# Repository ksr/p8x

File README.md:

# P8X — Hand-Built 8-Bit TTL CPU

A from-scratch 8-bit CPU built from ~130 74HCT logic chips on an 8-slot DIN41612 backplane. Fully microcoded; the microcode ROM images burned to the EPROMs are the same images the emulator interprets.

The machine now exists **twice**: as the TTL card set, and as an [FPGA
implementation](fpga/) of the same microarchitecture that boots the same
unmodified monitor, OS and toolchain. Both run the microcode from
`microcode/genucode.py`, and the C emulator is the golden reference for both.

The FPGA build also carries a **PGC-class graphics engine** (480x272
RGB565 panel, hardware 3D transforms, command lists, a fabric-parsed
graphics language modeled on the Matrox PG-640A) — see the
[theory of operation](docs/p8x-graphics-theory.md) and the
[graphics programmer's guide](docs/p8x-graphics-guide.md).

New to the abbreviations and signal names? See [GLOSSARY.md](GLOSSARY.md).

**Who made it:** I designed P8X, and it runs on an FPGA. Claude, Anthropic's AI, has been directly involved in its design, coding and documentation. — Ken Rother

## Architecture

- **8-bit data bus, 16-bit address bus**
- **4 × 16-bit pointer registers** (74169 up/down counters): P0 = PC, P1/P2 = general-purpose, P3 = stack pointer (empty-descending). The address bus is *always* driven by one of these — no separate MAR.
- **Registers:** A, B (ALU operands), T/T2 (hidden microcode temporaries), FLAGS (C, Z, N, V)
- **ALU:** 2 × 74181 + 74182 carry-lookahead, with a post-ALU shifter
- **Microcoded control:** 4 × 28C64 EEPROMs; ROM address = IR | step<<8 | cond<<12; **143 opcodes** defined in `microcode/genucode.py` (256 encodings available)
- **Memory map (rev E):** `$0000–$17FF` ROM (6 KB; shrunk from 8 KB 2026-09-14), `$1800–$FEFF` RAM (2× 62256; $1800–$1FFF is a scratch island), `$FF00–$FFFF` I/O (every data address is single-sourced in [`generators/gen_memmap.py`](generators/gen_memmap.py) → `memmap.inc`/`.h`/`.py`; commands pull the scratch/graphics/TPA-base symbols via `//#use mem`)

## Cards

The TTL machine is six core cards plus a PS/2 input card on the backplane, and a
bus test card for bring-up. Every board is designed and routed in **KiCad** (4-layer;
the plug-in cards are 280 × 140 mm) with orderable Gerbers in `hardware/<board>/kicad/`;
none has been fabricated yet. See [hardware/KICAD-BOARDS.md](hardware/KICAD-BOARDS.md)
and [hardware/RECONCILIATION.md](hardware/RECONCILIATION.md) (build readiness).

| Card | Function |
|------|----------|
| Control / Microcode | Clock, reset, sequencer, microcode EPROMs, IR, condition mux, front-panel |
| Register Bank | P0–P3 16-bit pointer registers, address bus drivers |
| ALU | A, B, T, T2 registers; 74181 ALU; shifter; FLAGS |
| Memory | 28C256 EEPROM (6 KB ROM window) + 2× 62256 SRAM, address decode (rev F) |
| I/O | Switches, LEDs, bus monitor, two 6850 ACIAs (RS-232, two DB9s) |
| CF-IDE | Two CompactFlash drives in 8-bit True IDE mode, at $FF10–$FF17 and $FF18–$FF1F |
| PS/2 | Keyboard + mouse ports at $FF58–$FF5F; an ATmega1284P behind a latch bridge |
| Bus test | Bring-up tool: a Raspberry Pi Pico drives the bus one microcycle at a time over USB |

The cards plug into a passive 8-slot backplane over a 96-pin DIN 41612 bus (rev C2).
The Eagle CAD of the first board generation is frozen (rev E) in each board's
`eagle-deprecated/` directory.

## Toolchain

| Tool | Location | Purpose |
|------|----------|---------|
| `microcode/genucode.py` | `microcode/` | Microcode generator → `u0–u3.bin` EPROM images |
| `assembler/p8xasm.py` | `assembler/` | Two-pass assembler, shares opcode table with genucode.py |
| `emulator/p8xemu.c` | `emulator/` | Cycle-accurate emulator, interprets the same u0–u3.bin images |
| `firmware/p8xmon.asm` | `firmware/` | ROM monitor (E/D/I/F/B/G/? commands) + BIOS jump table at `$0100` |
| `os/p8xos.asm` | `os/` | P8X/OS, RAM-resident disk OS booted from CF ([guide](os/README.md)) |
| `tools/p8xfs.py` | `tools/` | Host-side P8XFS disk-image tool (create/boot/put/get/ls) |
| `basic/p8xbasic.asm` | `basic/` | BASIC interpreter — disk-bootable or run-from-OS builds ([guide](basic/README.md)) |
| `apps/p8xedit.asm`, `apps/p8xasm.asm`, `apps/p8xcc.asm` | `apps/` | On-target toolchain: line editor + native two-pass assembler + native C compiler (`cc`), as `/bin` programs ([guide](apps/README.md)) |
| `compiler/p8cc.py` | `compiler/` | C cross-compiler (subset) → P8X asm → RUNnable `.bin` ([guide](compiler/README.md)) |
| `generators/gen_p8xopc.py` | `generators/` | Opcode table for the native assembler, generated from `genucode.OPC` |
| `generators/gen_eagle.py` | `generators/` | The canonical board netlists (`CARDS`, `busnet()`); its Eagle output is frozen at rev E |
| `generators/gen_kicad.py`, `build.sh` | `generators/` | KiCad boards from those netlists: placement, Freerouting, Gerbers, and the ERC/DRC readiness check |

**Generators are canon.** Never hand-edit board files (`.kicad_pcb`, and the frozen Eagle `.sch`/`.brd`) or ROM binaries — they are build artifacts. Edit the generator and regenerate. See [generators/README.md](generators/README.md) for what each script does and how to run it.

## Quick Start

Setting up a new machine? See [SETUP.md](SETUP.md) for the full toolchain, tier by
tier, and run `python3 tools/setup_check.py` to see what is installed and what each
work area still needs. Only the core-software tier is required to build and test.

```sh
# Build the emulator and regenerate microcode images
cd emulator && make

# Run the smoke tests (message print, JSR/RTS round-trip, branch countdown)
make test

# Rebuild a KiCad board: placement -> Freerouting -> Gerbers + renders -> the
# ERC/gate-sim/DRC/keepout/fab readiness check (needs KiCad 10 and a Freerouting
# jar; `all` builds every board). The netlists come from generators/gen_eagle.py.
cd ..
sh generators/build.sh memory-card
sh generators/check_card.sh memory-card          # the readiness check alone

# Reference PDFs (run from anywhere):
cd hardware
python3 ../generators/gen_bus_pdf.py              # bus definition PDF (hardware/backplane/)
python3 ../microcode/gen_progguide.py             # programmer's guide (-> docs/)
```

### EEPROM / programmer images

Both build paths emit **Intel HEX** alongside the raw `.bin`, for loading into an
EEPROM programmer:

- **Microcode** — `microcode/genucode.py` writes `u0–u3.bin` (what the emulator
  and tests load); the matching Intel HEX for the four 28C64 control-store EPROMs
  is produced into `rom/` by `make rom` (see below).
- **Program ROM** — the assembled monitor + BIOS for the 28C256 at `$0000`
  (about 4.9 KB of the 6 KB window; BASIC is no longer ROM-resident). `make rom` builds it into `rom/`.
- **Any other binary** — `python3 tools/bin2hex.py in.bin out.hex [base]`
  (e.g. a monitor built directly with `p8xasm.py`).

For a ready-to-burn set at fixed paths, run `cd emulator && make rom` (or
`sh tools/build_rom.sh`). It refreshes the four control-store EPROMs in
`microcode/` and writes the program ROM to `rom/p8x-prog-rom.{bin,hex}`. Both
are committed; see [rom/README.md](rom/README.md) for the chip map.

## Documentation

The documents below are also built into the project website, [p8x.cottageworker.com](https://p8x.cottageworker.com) (`website/`, MkDocs; published on every push to `main`).

| Document | Description |
|----------|-------------|
| [hardware/backplane/p8x-bus-definition.md](hardware/backplane/p8x-bus-definition.md) | Authoritative 96-pin bus pinout, signal descriptions, DOE/DLD encoding, microcode word layout |
| [hardware/backplane/p8x-backplane-design.md](hardware/backplane/p8x-backplane-design.md) | PCB stackup, termination analysis, BOM |
| [docs/p8x-card-standards.md](docs/p8x-card-standards.md) | Design rules that apply to every plug-in card |
| [docs/p8x-system-design.md](docs/p8x-system-design.md) | System and card-by-card architecture reference |
| [hardware/cf-card/p8x-cf-os-design.md](hardware/cf-card/p8x-cf-os-design.md) | CF-IDE hardware + P8X/OS design |
| [hardware/cf-card/p8xfs-v2-hierarchical.md](hardware/cf-card/p8xfs-v2-hierarchical.md) | P8XFS v2 hierarchical filesystem spec |
| [docs/p8x-programmers-guide.pdf](docs/p8x-programmers-guide.pdf) | Generated instruction set reference |
| [basic/p8x-basic-guide.md](basic/p8x-basic-guide.md) | P8X BASIC language reference (statements, expressions, graphics, examples) |
| [fpga/README.md](fpga/README.md) | FPGA build: milestones, getting started, both paths |
| [fpga/docs/architecture.md](fpga/docs/architecture.md) | FPGA module hierarchy, peripheral map, graphics, co-sim spec |
| [fpga/rtl/README.md](fpga/rtl/README.md) | What is shared vs sim-only, and the `cen` / `sc_en` contracts |
| [fpga/sim/README.md](fpga/sim/README.md) | How the co-sim trace-diff works, and the graphics frame diff |
| [BACKLOG.md](BACKLOG.md) | Live work only: NEXT / IDEAS / VERIFY / WONT-DO |
| [BACKLOG-DONE.md](BACKLOG-DONE.md) | Completed work + the project log |

### Per-card guides

Each board has its own directory under `hardware/` holding everything about it —
the KiCad board and its Gerbers, placement PDF and renders (`kicad/`), a README
explaining how the circuit works chip by chip, any board-specific design docs, and
the frozen Eagle files (`eagle-deprecated/`):

| Card | Directory |
|------|-----------|
| Control / Microcode | [hardware/control-card/](hardware/control-card/README.md) |
| Register Bank | [hardware/regbank-card/](hardware/regbank-card/README.md) |
| ALU | [hardware/alu-card/](hardware/alu-card/README.md) |
| Memory | [hardware/memory-card/](hardware/memory-card/README.md) |
| I/O | [hardware/io-card/](hardware/io-card/README.md) |
| CF-IDE | [hardware/cf-card/](hardware/cf-card/README.md) |
| PS/2 | [hardware/ps2-card/](hardware/ps2-card/README.md) |
| Bus test | [hardware/bustest-card/](hardware/bustest-card/p8x-bustest-card-design.md) |
| Backplane | [hardware/backplane/](hardware/backplane/p8x-backplane-design.md) |

## FPGA implementation

A standalone [FPGA build](fpga/) on a **Sipeed Tang Nano 20K** (Gowin GW2AR-18)
runs the whole machine — CPU, memory, ACIA console, microSD disk, and a 4.3"
480x272 graphics panel — from one chip and a USB cable. It is a **parallel track to the TTL build, not a replacement**:
same horizontal microcode word, same sequencer, same pointer/address model, so
the monitor, OS, BASIC, C compiler and assembler run **unmodified**.

| Milestone | State |
|-----------|-------|
| 0 First light (UART echo + heartbeat) | done |
| 1 CPU core in simulation, all 88 opcodes of the time | done |
| 2 ACIA + driven console in simulation | done |
| 3 Core on real hardware, full 64K map | done |
| 4 microSD disk — P8X/OS boots from card | done |
| 5 Clock-up + IRQ | next |
| 6 Graphics: 480x272 panel + drawing engine | done |

As built: **9 MHz** effective (27 MHz fabric, three phases per microcycle). The
CPU-only build is 40/46 block RAMs at ~48 MHz Fmax; adding the graphics panel takes
it to 44/46 and 13288/20736 LUT4, with Fmax measured at 38.8 MHz — still four times
the clock it runs at. P8X is programmed into the board's flash, so it comes up
standalone on power.

**Graphics** (`build.sh lcd`) adds the panel's native 480×272 framebuffer in
**RGB565 direct colour** — a pixel IS its colour, 65,536 of them — living in
the Tang Nano's in-package SDRAM behind a streaming controller, with a drawing
engine driven by BASIC in one window-space coordinate system (y up, the
PGC's own): `COLOR r,g,b` (or one packed value), `CLS`, `PIXELW`, `LINE`,
`BOX`, `CIRCLE` (a second radius gives an ellipse), `IMAGE` (draws a
P8I picture file — `tools/p8img.py` converts anything into one), the
`PIXELR(x,y)` and `RGB(r,g,b)` functions — plus the full PGC graphics
language as native statements (`MOVE`/`DRAW`/`POLY`/`RECT`, matrices, 3D,
command lists; see `man basic`). Text is the PGC's own stroke `TEXT`,
drawn card-side from the font the OS streams from `/FONT.GL` at boot
(GTEXT and its software rasterizer retired 2026-09-01). The drawing
statements emit that language; the engine lives in the device, so a
filled box costs the same handful of instructions as an empty one.
There is one geometry and no modes or palette to manage.
The same device is modelled in `p8xemu`, and the two are byte-compared frame
by frame.

**3D** (stages 7–8, `fpga/tang-nano-20k/sdram/STAGE*.md`): a wireframe
pipeline available three ways from C — all in software (`//#use gfx` +
`//#use g3d`), accelerated by the **MDU** (a memory-mapped hardware
multiply-divide unit at `$FF30`), or fully in fabric via the **geometry
engine** (`$FF40`): edge lists in SDRAM, an S7.8 matrix, one command to
transform/clip/project/draw, and page-flipped double buffering. The same
program picks the fastest fitted path at runtime; `cube` on the shipped disk
demonstrates all of them (`man cube`, `man g3d`).

**Verification is the point.** Every milestone is "make the RTL match the
emulator": the same program runs on both and their per-cycle architectural state
is diffed, so a divergence is a bug with an exact microcycle and signal rather
than a mystery. `fpga/sim/isa_test.asm` drives the original 88 opcodes through that diff;
the 55 added since are microcode only (no new hardware), and the RTL runs them from
the same images.

```sh
fpga/sim/run.sh 60000 isa_test.asm          # co-sim, the original 88 opcodes
fpga/sim/console.sh "" os/run-disk.img      # interactive console on the RTL
fpga/tang-nano-20k/build.sh cpu load        # build + program the board
```

## Status

- Emulator working: 143 opcodes, ACIA on stdin/stdout, CF-IDE disk model (`-c `), interactive I/O card (switches `-s`, LED trace `-L`), verified against microcode images
- Assembler working: two-pass, full expression support, shares opcode table with microcode generator
- KiCad boards designed and routed for the six CPU cards, the PS/2 card, the bus test card and the backplane (9 boards, 0 unconnected, Gerbers in each `kicad/`); none fabricated yet. The Eagle files of the first generation are frozen in `eagle-deprecated/`. (The standalone LED test card was a CAD-workflow trial, never built — deprecated and moved to `hardware/deprecated/led-card/`; its I/O address `$FF0C` is now free.)
- ROM monitor boots in the emulator; its filesystem hooks (`I`/`F`/`B`) run end to end against a CF image (`make test-cf`)
- P8X/OS v1.0 — full shell over flat **and hierarchical (P8XFS v2)** volumes. Built-in commands: `cd`/`mkdir`/`rmdir`/`load`/`run`/`save`/`del`/`path`/`pack`/`fsck`/`format`/`mount`/`umount`/`help`/`exit`/`man`/`sh`/`make`/`bootload` (`make` builds a target from a CWD `Makefile`; `bootload file` installs a freshly-built OS image into the boot sectors so the next `exit`+`B` runs it — the on-target OS-update step, closing the self-hosting loop) (the minimal-kernel split moved the pure-viewer/memory commands to `/bin`, including `dump`/`dep` — only `pack`/`fsck` remain resident because they mutate/scan the filesystem). **Dual CompactFlash** — a second card is **mounted at `/d1`** in one unified namespace (drive 0 is the root), so ordinary paths reach it with drive-unaware commands: `cd /d1`, `cat /d1/NOTES`, `grep x /d1/SRC/*.C`, cross-mount `cp /d1/A /B`. A single mount redirect in `FRESOLVE`/`RV_START` does the routing; **`cp -r /d1/dir /dir`** recursively copies a subtree across the mount (card provisioning), creating directories via the `SYS_MKDIR` syscall. **Userland commands in `/bin`** (written in C, run by bare name via implicit RUN + a `/bin` search PATH, or explicit `run`): **`dir`/`pwd`/`tree`/`cat`/`wc`/`grep`/`cp`/`mv`/`head`/`tail`/`more`/`sort`/`uniq`/`sed`/`awk`/`find`/`diff`/`cmp`/`vi`/`touch`/`man`/`dump`/`dep`/`examine`/`disasm`** (`dir README.TXT` lists a file / `dir R*` a glob, `dir -R`, `cp -r`, a VT100 `vi` screen editor, `man <cmd>` reading `/man`, `awk '{print $2}'` field processing, `examine` = interactive memory examine/modify like the monitor's `E`, etc.) — see [os/commands/](os/commands/README.md). Path resolution + CWD-path prompt; I/O redirection (`<`/`>`) and two-stage pipes (`a | b`); line editing (backspace/DEL, Ctrl-D EOF, **up/down-arrow command history** — an 8-line RAM ring — and **Tab autocomplete** of commands/paths with common-prefix fill + a match list on the second Tab); **`pack`** compacts the directory tree and **`fsck`** checks integrity on-target; host-side `p8xfs.py` builds (`--v2`), navigates, and `fsck`s images (`make test-os`)
- BASIC builds two ways from one source: disk-bootable (`B`) and a run-from-OS TPA program (`run BASIC.bin`) — `make test-basic` (ROM-resident BASIC was removed to reclaim ROM space; the old standalone `$0000` build was retired in 2026-08 when BASIC's console I/O moved onto the BIOS, which needs the monitor resident)
- On-target toolchain: **EDIT** (line editor) + **ASM** (native two-pass assembler) + **CC** (a from-scratch C compiler written in asm) as `/bin` programs — edit → **compile (`cc x.c >x.asm`)** → assemble → run a program entirely on the machine; ASM output is byte-identical to the host assembler across the whole opcode table (`make test-os`, see [apps/](apps/README.md)). **Rebuild any command on-target** — every command's source rides along under `/src/commands/{c,asm}` (plus shared `lib_*` helpers), each dir carrying a real **`Makefile`** (`target: deps` + TAB recipe, with `all`/`clean`/`install` targets). The **`make`** built-in reads the CWD `Makefile`, resolves prerequisites depth-first (shared deps built once), and drives `cc`→`asm` (or `asm` alone): `cd /src/commands/c && make pwd` rebuilds one command, `make all` the whole dir into `bin/`, `make install` publishes them over `/bin`, `make clean` removes the build outputs — see [os/commands/](os/commands/README.md). (P8X shell scripts end in `.sh`; `make` uses proper Makefiles.)
- **Native C compiler — Milestone B achieved.** `apps/p8xcc.asm` (`/bin/cc`) is a from-scratch, single-pass C compiler written directly in assembly, small enough to compile C **entirely on the machine** (front *and* back end) where the optimizing `p8cc.c` codegen — ~82 KB, larger than the whole 64 KB address space — never could. Through v0.28 it covers: functions, direct **and mutual** recursion, pointers + pass-by-reference, `int`/`char` arrays with `[]` and decay, **structs** (`.`/`->`), globals, the full operator set (`+ - * / % << >> & ^ | && || ?:`, `++`/`--`/`+=`/`-=`, comparisons, unary `- ! * &`), hex/char/string literals with escapes, `//`+`/* */` comments, a recursive **`//#use`** preprocessor (splices `/lib/lib_*.c`) plus object-like **`//#define`** macros (e.g. `//#use abi` names the BIOS/OS addresses so a command writes `bios(FOPEN, RDBUF, 0)`), and the `putchar`/`puts`/`getchar`/`peek`/`poke`/`argstr`/`bios` builtins. It compiles real OS command source: **`pwd.c` → `cc` → `asm` → runs** correctly on-target. Known gaps are listed under "cc — KNOWN LIMITATIONS" in `BACKLOG-DONE.md` (with the Milestone A/B record).
- **Host C compiler** — `compiler/p8cc.py` (the primary build tool: every `/bin` command is compiled with it) plus `compiler/p8cc.c`, the same compiler rewritten in its own subset that **self-compiles** ("small C in small C", Milestone A). Full subset incl. `struct`/`union`, global initializers, and the operators above (`make test-c`, host-vs-self differential `c_selfhost_test`, see [compiler/](compiler/README.md)).
- BIOS **file API**: byte streams (`FOPEN`/`FGETB`, `FWOPEN`/`FPUTB`/`FCLOSE`), path resolution into subdirectories (`FRESOLVE`), name formatting (`FNORM`), and directory iteration (`FOPENDIR`/`FNEXT`) — the assembler rides on the streams and self-hosts (`make test-cf`)
- **FPGA (Tang Nano 20K):** the same microarchitecture in Verilog, verified against the emulator cycle-for-cycle across the original 88 opcodes, then run on real hardware — monitor over USB serial, full 64K map, and **P8X/OS booting from a microSD** with the whole `/bin` toolchain. The board wrote its own disk: `fpga/tang-nano-20k/tools/imgload.asm` streams a P8XFS image over the console and writes it with `CFWRITE`, so no host root or card reader is needed. See [fpga/](fpga/README.md)
- **Next:** multi-stage pipes (`a | b | c`); open-by-name as one syscall (`SYS_OPEN`); the IRQ-controller hardware card; hardware bring-up (DIN 41612 footprint check against the physical connectors, order the backplane first); FPGA milestone 5 (clock-up + IRQ). Current state in [docs/p8x-status.md](docs/p8x-status.md), the working list in [BACKLOG.md](BACKLOG.md)

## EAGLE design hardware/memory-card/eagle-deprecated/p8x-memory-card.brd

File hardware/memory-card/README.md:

# Memory Card

> **Theory of operation:** [p8x-memory-card-theory.md](p8x-memory-card-theory.md) — deep walkthrough of inputs/outputs, signal flow, and logic.

Provides the system's ROM and RAM and gates them onto the data bus. It decodes the
address bus to pick ROM vs RAM, keeps both off the data bus during I/O accesses,
and generates a clean write strobe.

> **Build the KiCad rev F board.** The 2026-09-14 ROM shrink made the map
> **6 KB ROM `$0000–$17FF`** with **`$1800–$1FFF` a RAM scratch island** (written
> by the OS/BIOS, so it must be RAM). The KiCad board in [`kicad/`](kicad/README.md)
> (rev F, routed, not yet fabricated) implements that decode on three spare gates,
> with no new chips: ROM `!CE` gains an `A11·A12` term and low-RAM U10 widens to
> `$1800–$7FFF`. The chip-by-chip text below describes the **rev E** netlist in
> `gen_eagle.py` (8 KB ROM, `$0000–$1FFF`), which `kicad/mem_revf.py` rewires to
> rev F for both the KiCad board and its schematic; the frozen Eagle `.sch` in `eagle-deprecated/` is rev E too and
> must not be built.

| Region | Device | Size |
|--------|--------|------|
| `$0000–$17FF` | 28C64 ROM (U1) | 6 KB — monitor + BIOS (BASIC is a disk program) |
| `$1800–$1FFF` | 62256 SRAM (U10) | 2 KB scratch island (IBUF/SBUF/BIOS scratch) |
| `$2000–$7FFF` | 62256 SRAM (U10) | 24 KB |
| `$8000–$FEFF` | 62256 SRAM (U2) | 32 KB (minus the I/O page) |
| `$FF00–$FFFF` | — (I/O page) | RAM inhibited; handled by I/O & CF cards |

(Rev E after the 2026-09-14 shrink: 6 KB ROM at `$0000–$17FF`; two 62256 cover
`$1800–$FEFF` = 58 KB; OS loads at `$2000`.)

> This README describes the circuit as actually built in
> [`generators/gen_eagle.py`](../../generators/gen_eagle.py). See
> [p8x-system-design.md §6](../../docs/p8x-system-design.md) for the overview and
> [p8x-bus-definition.md](../backplane/p8x-bus-definition.md) for bus pins.

## Chip inventory

| Ref | Device | Role |
|-----|--------|------|
| U1 | 28C256 (low 8 KB used; or a 28C64) | ROM (rev E: 8 KB, $0000–$1FFF; rev F: 6 KB, $0000–$17FF) |
| U2 | 62256 | SRAM, 32 KB (`$8000–$FEFF`) |
| U10 | 62256 | SRAM, 24 KB (`$2000–$7FFF`, rev E; `$1800–$7FFF` in rev F) |
| U3 | 74245 | Bidirectional data-bus transceiver |
| U4 | 7430 | 8-input NAND — I/O page ($FFxx) detector |
| U5 | 74138 | DOE decoder (read enable) |
| U6 | 74138 | DLD decoder (write strobe) |
| U7 | 74HCT00 | NAND — RAM chip-select logic |
| U8 | 74HCT32 | OR — write-strobe gating |
| U9 | 74HCT08 | AND — transceiver enable (rev F: spare gate U9.4 = `A11·A12`) |
| U11 | 74HCT32 | OR — ROM `!CE` (rev E: A13 OR A14 OR A15; rev F adds the `A11·A12` term on U11.2/U11.3) |

## How it works

### Address decode (ROM vs RAM vs I/O) — rev E, decoded from A13 + A14 + A15
- **ROM** (U1) is selected when **A13 = A14 = A15 = 0** — `!CE = A13 OR A14 OR A15`,
  so the ROM responds for `$0000–$1FFF` (8 KB).
- **Low RAM** (62256, U10) is selected when **A15 = 0 and (A13 or A14) = 1** —
  `!CE = A15 OR NOR(A13, A14)`, covering `$2000–$7FFF` (deselected in the
  `$0000–$1FFF` ROM page).
- The **I/O page detector** (U4, a 7430 8-input NAND on A8–A15) asserts `-IOPG` low
  whenever the address is `$FFxx`.
- **Main RAM** (62256, U2) is selected only when **A15 = 1 *and* not the I/O page**.
  U7 NANDs A15 with `-IOPG` to produce `-RAMCE`: RAM enables for `$8000–$FEFF` but
  stays off for `$FFxx`, leaving that page to the I/O and CF cards.

The rev-E decode adds the A13 term to the ROM/RAM-low select. rev D's spare gates
were used up, so rev E adds exactly one 2-input gate: **U11.1** (a 74HCT32 OR).
The rev-D gates are reused in place — `U8.4` now ORs `A13,A14` into `Q`; `U11.1`
ORs `Q` with `A15` for the ROM `!CE` (`A13|A14|A15`); and `U7.3` NANDs `!A15` with
`Q` for the RAM-low `!CE` (= `A15 OR NOR(A13,A14)`). U11's 100 nF cap is `C11`.

### Data-bus transceiver
The 74245 (U3) connects on-card memory to the backplane data bus. Its **direction**
is set by read vs write: on a read (DOE = 7 → `-RD`) it drives the bus from memory;
on a write (DLD = 7 → `-MEMW`) it drives memory from the bus. It is **enabled only
for on-card addresses** (`-BOE`, gated in U9), so the card never fights another
driver during I/O cycles.

### Read path
DOE code 7 (`-RD`, decoded by U5) drives the memory output-enables (`!OE`) and sets
the 74245 direction toward the bus. The selected chip (ROM or RAM, per the decode
above) puts its byte on the bus.

### Write path & strobe timing
DLD code 7 (`-MEMW`, decoded by U6) is the write request. The actual `!WE` strobe is
`-MEMW` **gated with CLK̄** in U8: this gives address and data a full half-cycle to
set up before the write pulse falls in the second half-cycle — clean, glitch-free
writes. Only RAM responds to writes; the EEPROM `!WE` is held inactive (in-system
EEPROM programming is out of scope for normal operation).

## Bus codes this card owns
- **DOE:** 7 = memory read (drives D0–D7)
- **DLD:** 7 = memory write (`MEMW` strobe) — shared decode convention with the I/O card

## LEDs
PWR (green), ROM (yellow), RAM (yellow), RD (green), WR (red) — show which region
and direction is active each cycle. **RAM2 (yellow, rev E)** lights when the new
`$2000–$7FFF` bank (U10) is addressed — a bank-select indicator (driven by U7's
spare gate inverting `-RAM2CE`; not `-BOE`-gated like the others, as only one
spare gate remained).

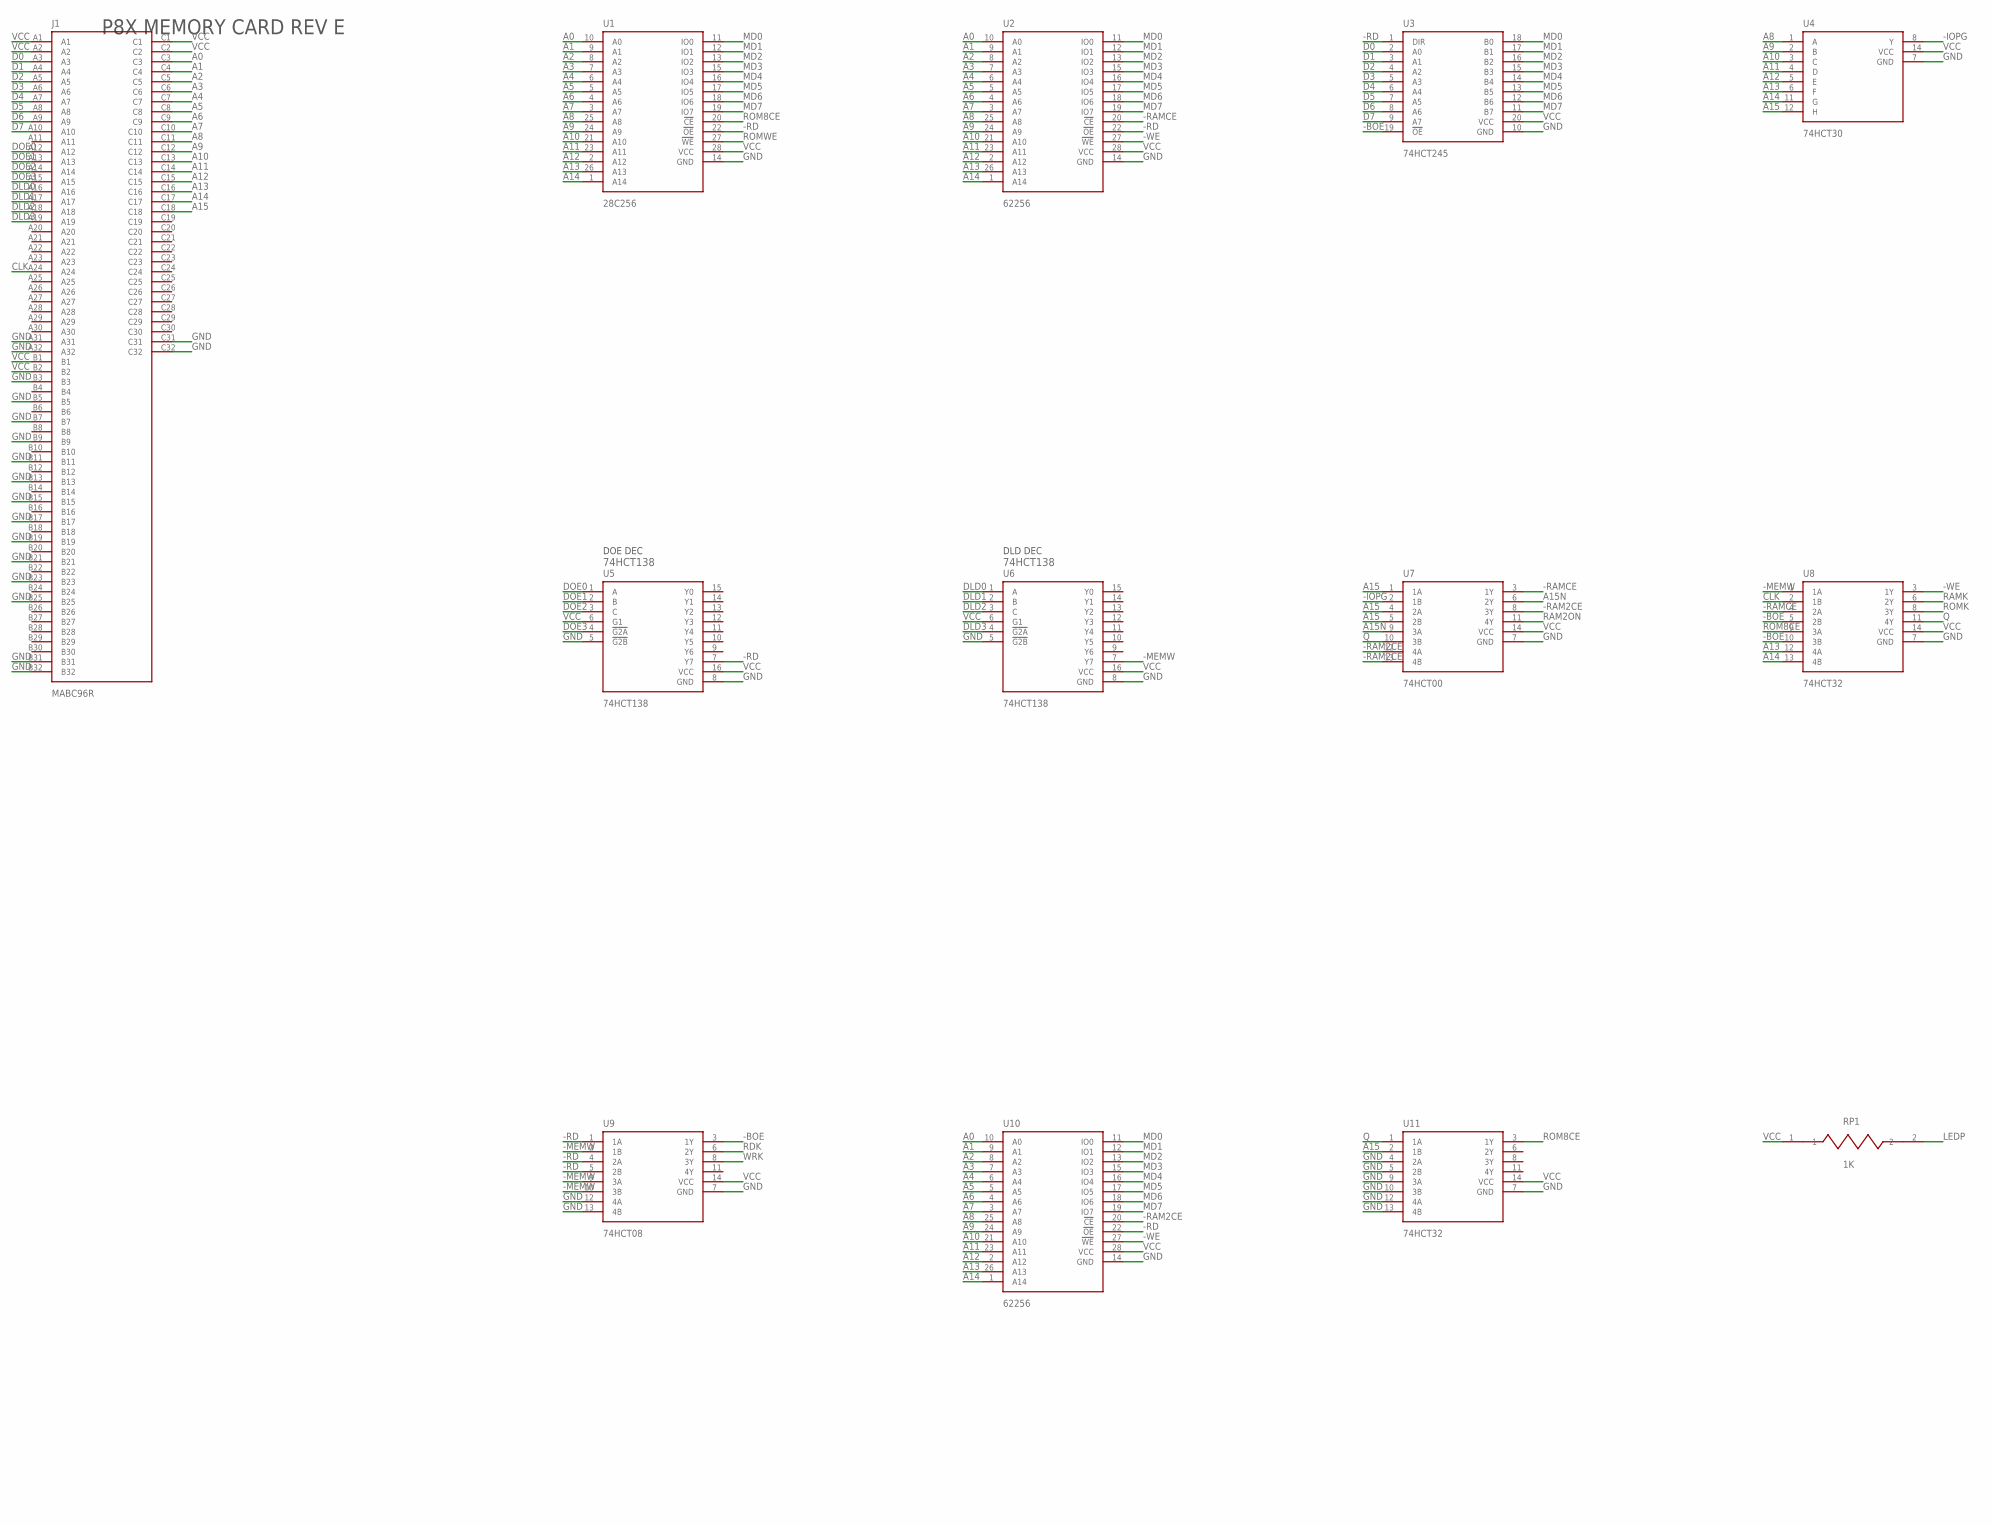
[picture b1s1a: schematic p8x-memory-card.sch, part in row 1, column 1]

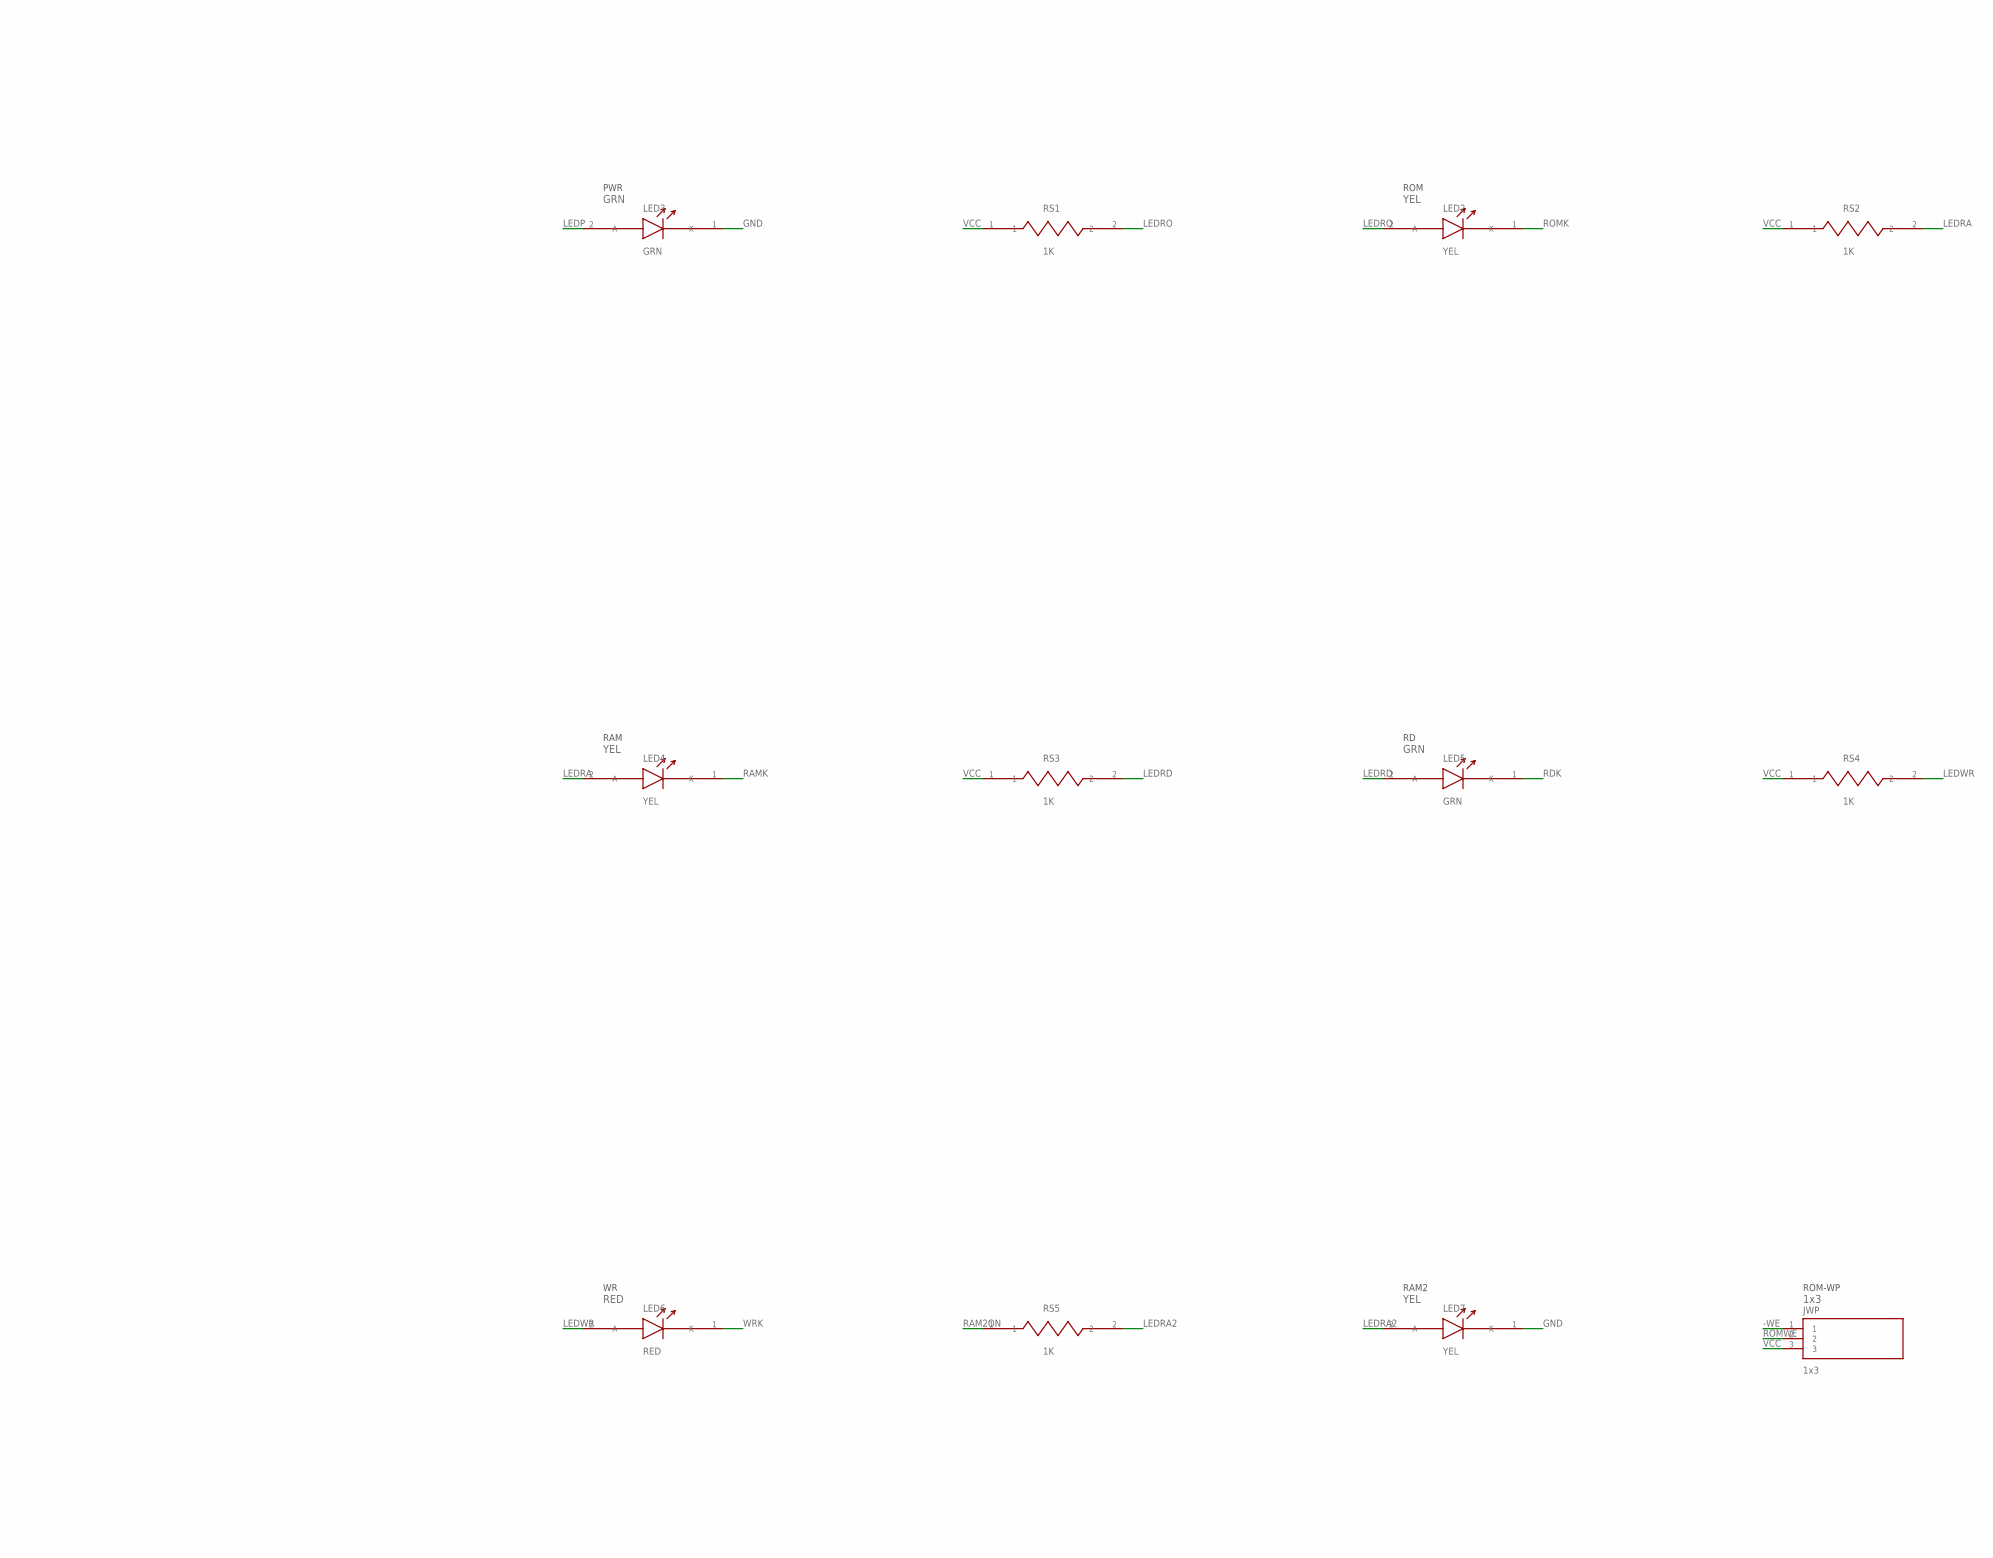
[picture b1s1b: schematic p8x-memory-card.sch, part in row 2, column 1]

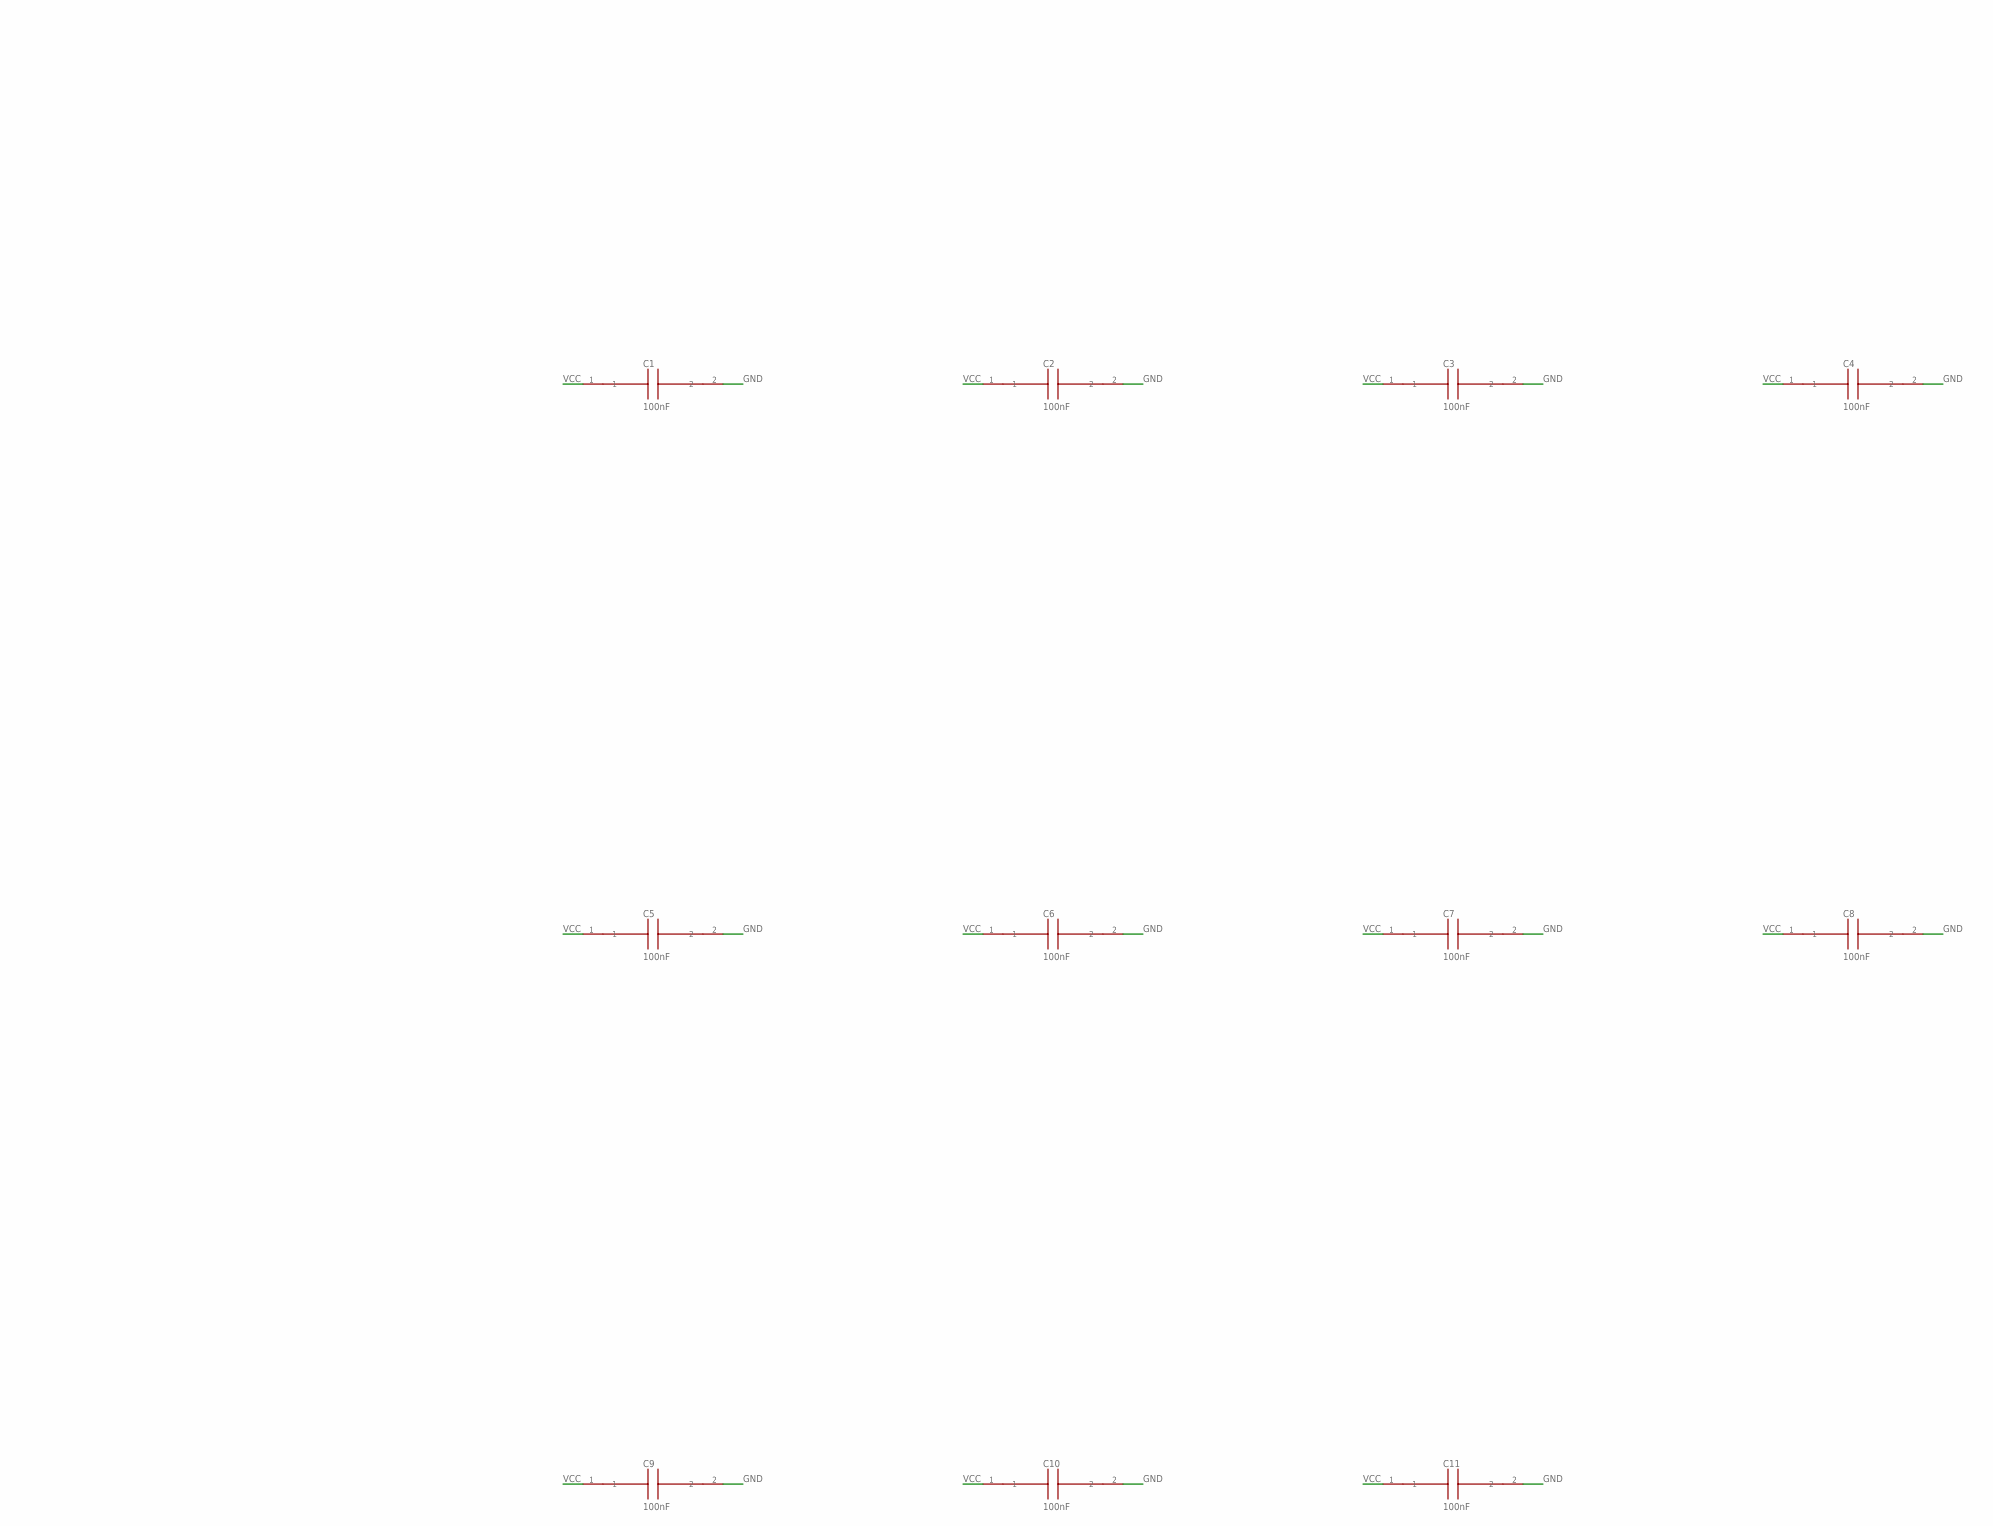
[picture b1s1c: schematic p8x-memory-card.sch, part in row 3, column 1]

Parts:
C1, C2, C3, C4, C5, C6, C7, C8, C9, C10, C11: 100nF; C_DISC1
J1: MABC96R
JWP: 1x3; HDR3
LED2, LED4, LED7: YEL; LED5
LED3, LED5: GRN; LED5
LED6: RED; LED5
RP1: 1K; R_AXIAL
RS1, RS2, RS3, RS4, RS5: 1K; R_AXIAL
U1: 28C256; DIP28W
U2, U10: 62256; DIP28W
U3: 74HCT245; DIP20
U4: 74HCT30; DIP14
U5, U6: 74HCT138; DIP16
U7: 74HCT00; DIP14
U8, U11: 74HCT32; DIP14
U9: 74HCT08; DIP14

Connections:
-BOE: U3.19 (!OE), U8.5 (2B), U8.10 (3B), U9.3 (1Y)
-IOPG: U4.8 (Y), U7.2 (1B)
-MEMW: U6.7 (Y7), U8.1 (1A), U9.2 (1B), U9.9 (3A), U9.10 (3B)
-RAM2CE: U7.8 (3Y), U7.12 (4A), U7.13 (4B), U10.20 (!CE)
-RAMCE: U2.20 (!CE), U7.3 (1Y), U8.4 (2A)
-RD: U1.22 (!OE), U2.22 (!OE), U3.1 (DIR), U5.7 (Y7), U9.1 (1A), U9.4 (2A), U9.5 (2B), U10.22 (!OE)
-WE: JWP.1, U2.27 (!WE), U8.3 (1Y), U10.27 (!WE)
A0: J1.C3, U1.10 (A0), U2.10 (A0), U10.10 (A0)
A1: J1.C4, U1.9 (A1), U2.9 (A1), U10.9 (A1)
A2: J1.C5, U1.8 (A2), U2.8 (A2), U10.8 (A2)
A3: J1.C6, U1.7 (A3), U2.7 (A3), U10.7 (A3)
A4: J1.C7, U1.6 (A4), U2.6 (A4), U10.6 (A4)
A5: J1.C8, U1.5 (A5), U2.5 (A5), U10.5 (A5)
A6: J1.C9, U1.4 (A6), U2.4 (A6), U10.4 (A6)
A7: J1.C10, U1.3 (A7), U2.3 (A7), U10.3 (A7)
A8: J1.C11, U1.25 (A8), U2.25 (A8), U4.1 (A), U10.25 (A8)
A9: J1.C12, U1.24 (A9), U2.24 (A9), U4.2 (B), U10.24 (A9)
A10: J1.C13, U1.21 (A10), U2.21 (A10), U4.3 (C), U10.21 (A10)
A11: J1.C14, U1.23 (A11), U2.23 (A11), U4.4 (D), U10.23 (A11)
A12: J1.C15, U1.2 (A12), U2.2 (A12), U4.5 (E), U10.2 (A12)
A13: J1.C16, U1.26 (A13), U2.26 (A13), U4.6 (F), U8.12 (4A), U10.26 (A13)
A14: J1.C17, U1.1 (A14), U2.1 (A14), U4.11 (G), U8.13 (4B), U10.1 (A14)
A15: J1.C18, U4.12 (H), U7.1 (1A), U7.4 (2A), U7.5 (2B), U11.2 (1B)
A15N: U7.6 (2Y), U7.9 (3A)
CLK: J1.A24, U8.2 (1B)
D0: J1.A3, U3.2 (A0)
D1: J1.A4, U3.3 (A1)
D2: J1.A5, U3.4 (A2)
D3: J1.A6, U3.5 (A3)
D4: J1.A7, U3.6 (A4)
D5: J1.A8, U3.7 (A5)
D6: J1.A9, U3.8 (A6)
D7: J1.A10, U3.9 (A7)
DLD0: J1.A16, U6.1 (A)
DLD1: J1.A17, U6.2 (B)
DLD2: J1.A18, U6.3 (C)
DLD3: J1.A19, U6.4 (!G2A)
DOE0: J1.A12, U5.1 (A)
DOE1: J1.A13, U5.2 (B)
DOE2: J1.A14, U5.3 (C)
DOE3: J1.A15, U5.4 (!G2A)
GND: C1.2, C2.2, C3.2, C4.2, C5.2, C6.2, C7.2, C8.2, C9.2, C10.2, C11.2, J1.A31, J1.A32, J1.B3, J1.B5, J1.B7, J1.B9, J1.B11, J1.B13, J1.B15, J1.B17, J1.B19, J1.B21, J1.B23, J1.B25, J1.B31, J1.B32, J1.C31, J1.C32, LED3.1 (K), LED7.1 (K), U1.14 (GND), U2.14 (GND), U3.10 (GND), U4.7 (GND), U5.5 (!G2B), U5.8 (GND), U6.5 (!G2B), U6.8 (GND), U7.7 (GND), U8.7 (GND), U9.7 (GND), U9.12 (4A), U9.13 (4B), U10.14 (GND), U11.4 (2A), U11.5 (2B), U11.7 (GND), U11.9 (3A), U11.10 (3B), U11.12 (4A), U11.13 (4B)
LEDP: LED3.2 (A), RP1.2
LEDRA: LED4.2 (A), RS2.2
LEDRA2: LED7.2 (A), RS5.2
LEDRD: LED5.2 (A), RS3.2
LEDRO: LED2.2 (A), RS1.2
LEDWR: LED6.2 (A), RS4.2
MD0: U1.11 (IO0), U2.11 (IO0), U3.18 (B0), U10.11 (IO0)
MD1: U1.12 (IO1), U2.12 (IO1), U3.17 (B1), U10.12 (IO1)
MD2: U1.13 (IO2), U2.13 (IO2), U3.16 (B2), U10.13 (IO2)
MD3: U1.15 (IO3), U2.15 (IO3), U3.15 (B3), U10.15 (IO3)
MD4: U1.16 (IO4), U2.16 (IO4), U3.14 (B4), U10.16 (IO4)
MD5: U1.17 (IO5), U2.17 (IO5), U3.13 (B5), U10.17 (IO5)
MD6: U1.18 (IO6), U2.18 (IO6), U3.12 (B6), U10.18 (IO6)
MD7: U1.19 (IO7), U2.19 (IO7), U3.11 (B7), U10.19 (IO7)
Q: U7.10 (3B), U8.11 (4Y), U11.1 (1A)
RAM2ON: RS5.1, U7.11 (4Y)
RAMK: LED4.1 (K), U8.6 (2Y)
RDK: LED5.1 (K), U9.6 (2Y)
ROM8CE: U1.20 (!CE), U8.9 (3A), U11.3 (1Y)
ROMK: LED2.1 (K), U8.8 (3Y)
ROMWE: JWP.2, U1.27 (!WE)
VCC: C1.1, C2.1, C3.1, C4.1, C5.1, C6.1, C7.1, C8.1, C9.1, C10.1, C11.1, J1.A1, J1.A2, J1.B1, J1.B2, J1.C1, J1.C2, JWP.3, RP1.1, RS1.1, RS2.1, RS3.1, RS4.1, U1.28 (VCC), U2.28 (VCC), U3.20 (VCC), U4.14 (VCC), U5.6 (G1), U5.16 (VCC), U6.6 (G1), U6.16 (VCC), U7.14 (VCC), U8.14 (VCC), U9.14 (VCC), U10.28 (VCC), U11.14 (VCC)
WRK: LED6.1 (K), U9.8 (3Y)

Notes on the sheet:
P8X MEMORY CARD REV E
DOE DEC
74HCT138
DLD DEC
PWR
GRN
ROM
YEL
RAM
RED
RAM2
ROM-WP
1x3

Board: 4 copper layers, 36 parts (0 on the bottom side), 65 nets, no tracks yet.
